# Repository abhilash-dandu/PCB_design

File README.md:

# PCB_design
A growing collection of modular electronics trainer projects, including timer circuits, microcontroller-based designs, and configurable PCB modules for learning and experimentation.

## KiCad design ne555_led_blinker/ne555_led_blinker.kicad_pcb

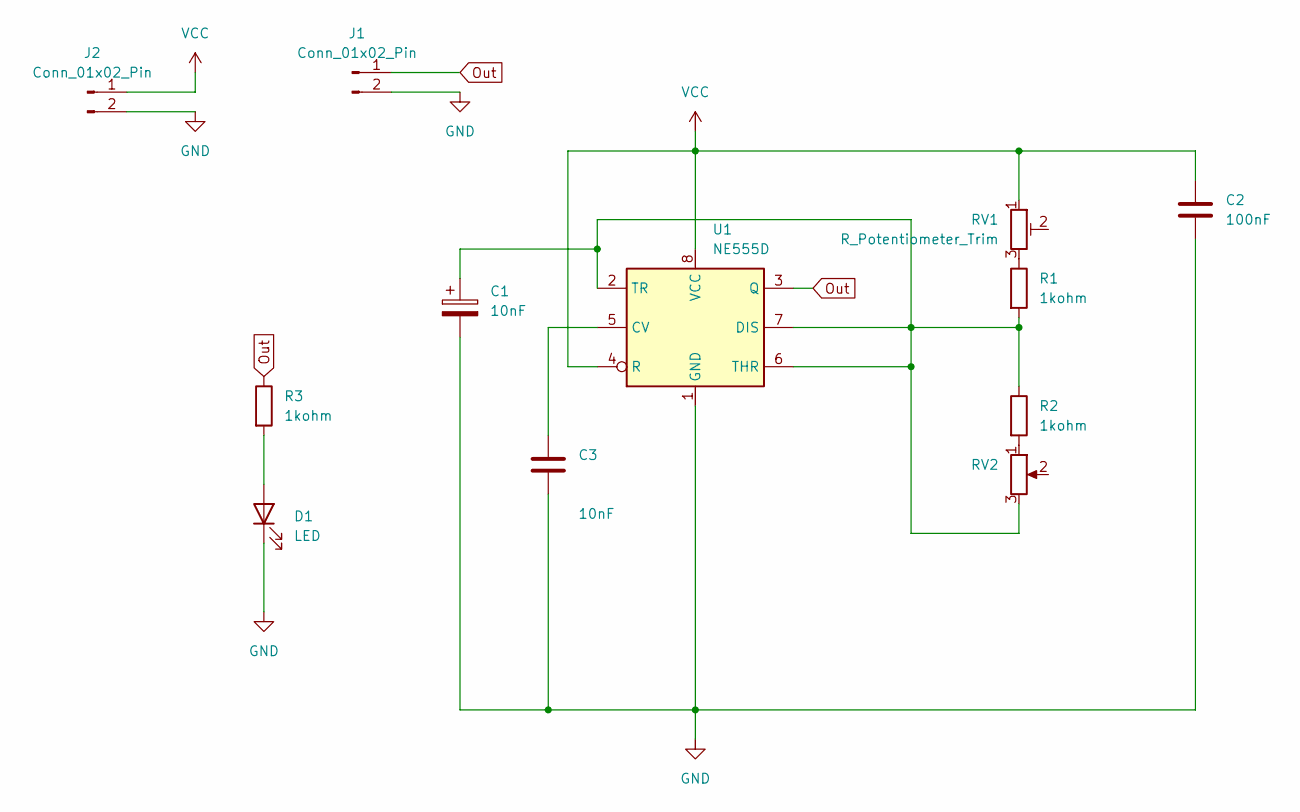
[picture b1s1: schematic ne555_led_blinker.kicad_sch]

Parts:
C1: 10nF; CP_Radial_D5.0mm_P2.50mm
C2: 100nF; C_Disc_D3.0mm_W2.0mm_P2.50mm
C3: 10nF; C_Disc_D3.0mm_W2.0mm_P2.50mm
D1: LED; LED_D5.0mm
J1, J2: Conn_01x02_Pin; PinHeader_1x02_P2.54mm_Vertical
R1, R2, R3: 1kohm; R_Axial_DIN0207_L6.3mm_D2.5mm_P7.62mm_Horizontal
RV1: R_Potentiometer_Trim; Potentiometer_Bourns_3296W_Vertical
RV2: R_Potentiometer; Potentiometer_Alpha_RD901F-40-00D_Single_Vertical
U1: NE555D; DIP-8_W7.62mm

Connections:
GND: C1.2, C2.2, C3.2, D1.1 (K), J1.2, J2.2, U1.1 (GND)
unnamed: D1.2 (A), R3.2
unnamed: R1.1, RV1.3
unnamed: R2.2, RV2.1
unnamed: C3.1, U1.5 (CV)
unnamed: C1.1, R1.2, R2.1, RV2.3, U1.2 (TR), U1.6 (THR), U1.7 (DIS)
Out: J1.1, R3.1, U1.3 (Q)
VCC: C2.1, J2.1, RV1.1, U1.4 (R), U1.8 (VCC)

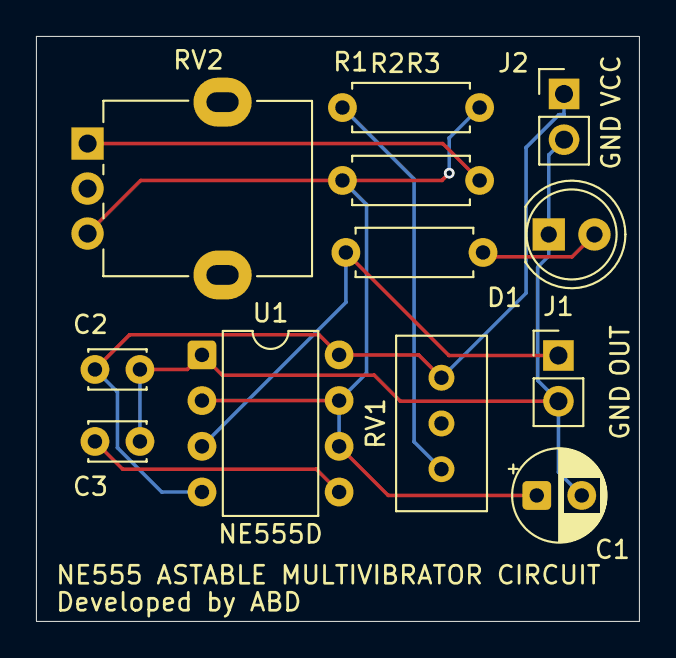
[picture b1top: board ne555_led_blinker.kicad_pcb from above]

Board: 2 copper layers, 33.5 x 32.5 mm, 12 parts (0 on the bottom side), 8 nets.

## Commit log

2026-01-18 Added ne555_led_blinker project
2026-01-18 Added voltage regulator and 555 blinker projects
